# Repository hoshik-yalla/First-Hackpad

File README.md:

# ⌨️ First-Hackpad: A 3-Key Mechanical Macro Pad

A compact, custom-designed three-key mechanical macro pad built using the Seeed Studio XIAO RP2040 microcontroller. This project helps learn the basics of PCB design, schematic layout, and planning while turning the idea into a simple hackpad.

## CAD

The STEP files for the case are in the [CAD](CAD) folder.

## PCB

## Usage
**Codebud** is a hackpad designed to help programmers in VS Code. Instead of navigating menus or remembering keyboard shortcuts, users can press dedicated keys to launch frequently used actions.

Key 1: Ctrl+Shift+P - Command Palette
Key 2: Ctrl+Alt+I - Copilot Chat
Key 3: Ctrl+Shift+` - Terminal

Please follow the readme in 'firmware' folder for installation instructions

## BOM

| Item | Quantity |
| --- | --- |
| Unsoldered Seeed XIAO RP2040 | 1 |
| MX-Style switches | 3 |
| 0.91 inch OLED display | 1 |
| White blank DSA keycaps | 3 |
| $15 PCB Grant | 1 |
| 3D Print | 1 |

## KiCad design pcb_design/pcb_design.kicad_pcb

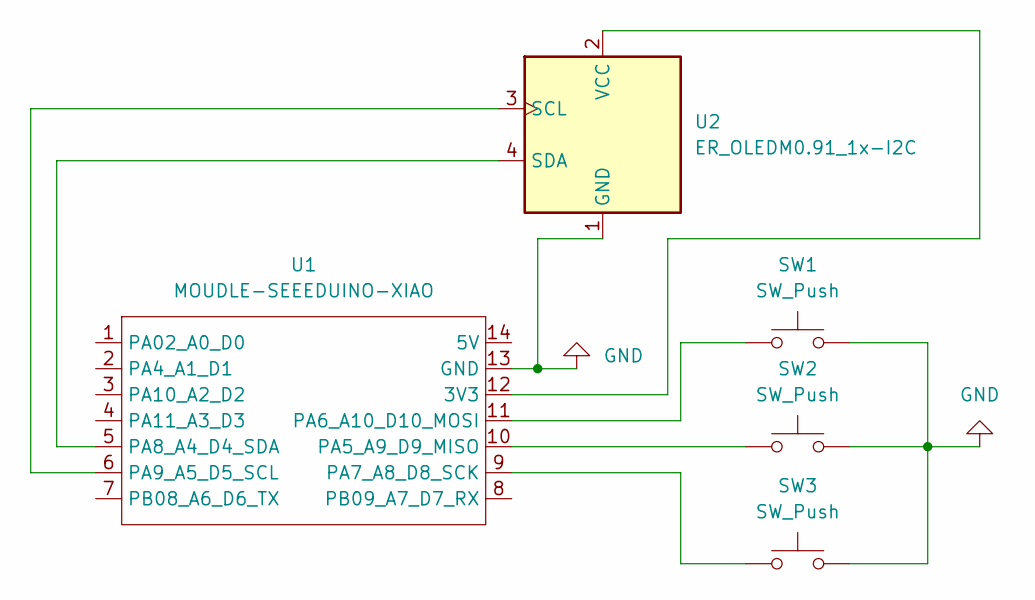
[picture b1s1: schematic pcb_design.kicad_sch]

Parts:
SW1, SW2, SW3: SW_Push; SW_Cherry_MX_1.00u_PCB
U1: MOUDLE-SEEEDUINO-XIAO; XIAO-Generic-Hybrid-14P-2.54-21X17.8MM
U2: ER_OLEDM0.91_1x-I2C

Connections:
GND: SW1.2, SW2.2, SW3.2, U1.13 (GND), U2.1 (GND)
unnamed: U1.12 (3V3), U2.2 (VCC)
unnamed: SW2.1, U1.10 (PA5_A9_D9_MISO)
unnamed: SW1.1, U1.11 (PA6_A10_D10_MOSI)
unnamed: SW3.1, U1.9 (PA7_A8_D8_SCK)
unnamed: U1.5 (PA8_A4_D4_SDA), U2.4 (SDA)
unnamed: U1.6 (PA9_A5_D5_SCL), U2.3 (SCL)

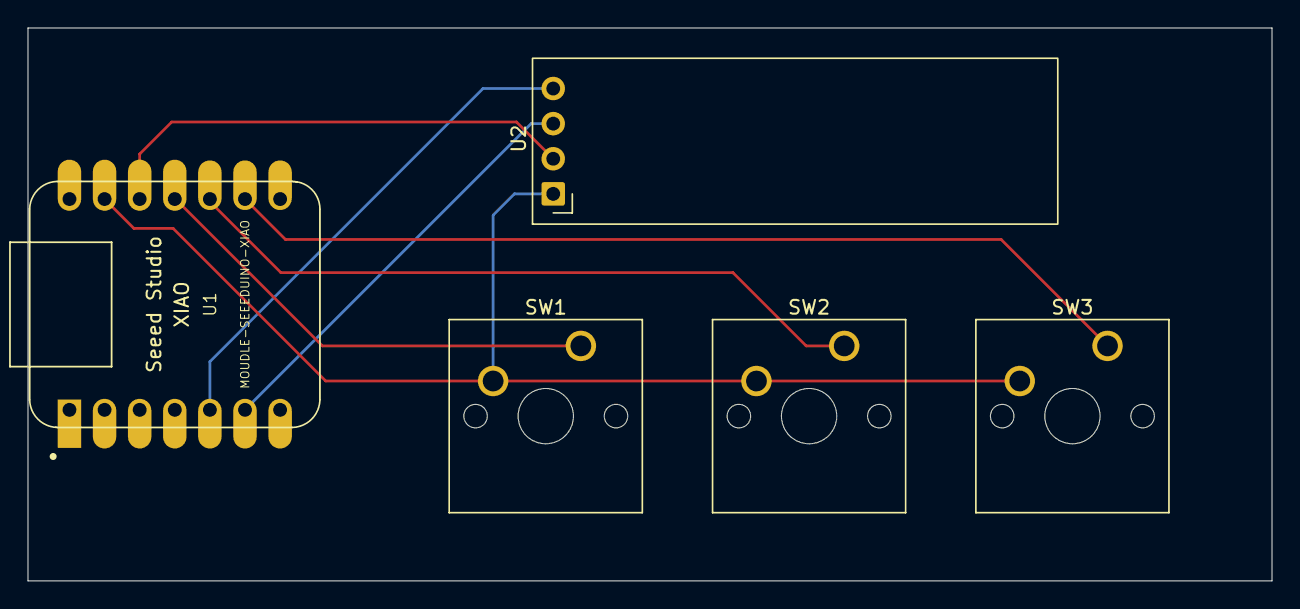
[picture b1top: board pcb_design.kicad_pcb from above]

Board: 2 copper layers, 90.0 x 40.0 mm, 5 parts (0 on the bottom side), 7 nets.

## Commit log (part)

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2026-06-08 Add initial schematic design and main Python script for project
    - Created a new KiCad schematic file with components including a push button switch and a Seeeduino XIAO module.
    - Added a new Python script to handle digital input/output using the board and digitalio libraries.
2026-06-10 Polish codebase: complete macro pad firmware, update KiCad project files, and add detailed README documentation with schematic/PCB renders
2026-06-10 Revert firmware implementation and adjust README to focus solely on hardware documentation
2026-06-10 chore: organize repository and fix KiCad git tracking
2026-06-29 Finalized PCB Design.
    1st Design Iteration - Followed the guide closely to understand the usage of KiCad.
    2nd Design Iteration - Discovered the DRC function which let me fix some issues with the PCB Design
    3rd Design Iteration - Redesigned the PCB to my own dimensions with a unique layout.
    4th Design Iteration - Added an OLED Display to the hackpad and tested with encoder, but figured it wasn't serving a key role in my planned use case.
    5th Design Iteration - Redesign the PCB to the newly discovered hackclub rules.
